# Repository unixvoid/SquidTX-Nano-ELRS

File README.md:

# SquidTX Nano

SquidTX Nano is a small 2.4Ghz ELRS TX board. It features an ESP32-WROOM-32E and an SX1280
and runs the stock ExpressLRS `DIY 2400 E28` target. An onboard TPS63802 buck-boost takes
1.3 V to 5.5 V and makes 3.3 V, so the board runs straight off a 1S battery. I designed
this to fit in a TBS Tango 2, but it'll work with anything.

The KiCad files, gerbers and photos are in this repo so you can build one.

<p align="center">
  
  <br>
  <em>Finished board, with the E28 module and its u.FL antenna</em>
  <br><br>

  <br>
  <em>Part-assembled front (E28-2G4M27S and u.FL antenna), part-assembled back (ESP32-WROOM-32E), bare PCB front, bare PCB back</em>
  <br><br>

  <br>
  <em>Copper and silkscreen: front (E28 side) and back (ESP32 side)</em>
  <br><br>
  
  <br>
  <em>Installed between the gimbals, with the three wires out to the module bay</em>
</p>

Full schematic: [docs/images/schematic.png](docs/images/schematic.png).

## Contents

- [Features](#features)
- [Specs](#specs)
- [Pin map](#pin-map)
- [Power](#power)
- [Connectors and wiring](#connectors-and-wiring)
- [Bill of materials](#bill-of-materials)
- [Firmware](#firmware)
- [Flashing](#flashing)
- [Manufacturing](#manufacturing)
- [Repo layout](#repo-layout)
- [License](#license)

## Features

- Runs the stock ExpressLRS `DIY 2400 E28` target.
- E28-2G4M27S does the RF: SX1280, PA and LNA, up to 27 dBm, with the PA and LNA enables driven by
  the firmware on IO26 and IO27.
- TPS63802 buck-boost, 1.3 V to 5.5 V in, 3.3 V out at up to 2 A, so no second regulator is needed.
- 20.0 x 35.5 mm, 2 layers, 1.6 mm FR-4, 0805 passives and a 1210 inductor.
- 6-pin SquidGrip pad array for the first flash and for recovery.
- Optional 2-pin fan header on IO17, which is the target's `misc_fan_en`.

## Specs

| Item | Value |
| --- | --- |
| Protocol | ExpressLRS 2.4 GHz, CRSF over a half-duplex UART |
| RF module | Ebyte E28-2G4M27S (SX1280 with PA and LNA), 2.4 to 2.5 GHz, 27 dBm |
| Antenna | u.FL/IPEX connector on the sx1280 module. I've used an external u.FL antenna in some of the photos |
| MCU | ESP32-WROOM-32E (ESP32-D0WD-V3, 4 MB flash) |
| Firmware target | `DIY 2400 E28`, legacy name `DIY_2400_TX_ESP32_SX1280_E28` |
| Minimum ExpressLRS version | 3.0.0 |
| Input voltage | 1.3 V to 5.5 V |
| Output | 3.3 V, up to 2 A (TPS63802DLAR buck-boost) |
| Power levels | 5, shown as 10 / 25 / 50 / 100 / 250 mW in the Lua script |
| Size | 20.0 x 35.5 mm, 0.5 mm corner radius |
| Connectors | J1 3-pin power and CRSF header, J2 2-pin fan header, SG1 6-pin SquidGrip port |
| LED, screen, button | none |

## Pin map

These are taken from the schematic, and they match the stock `DIY 2400 E28` target pin for pin,
which is why no firmware changes are needed.

### ESP32-WROOM-32E

| ESP32 pin | GPIO | Net name | Connects to | ELRS target key |
| --- | --- | --- | --- | --- |
| 29 | IO5 | `NSS_CTS/IO5` | E28 pin 6 (NSS_CTS) | `radio_nss: 5` |
| 30 | IO18 | `SCK/RTSN/IO18` | E28 pin 5 (SCK_RTSN) | `radio_sck: 18` |
| 31 | IO19 | `MISO_TX/IO19` | E28 pin 3 (MISO_TX) | `radio_miso: 19` |
| 37 | IO23 | `MOSI_RX/IO23` | E28 pin 4 (MOSI_RX) | `radio_mosi: 23` |
| 33 | IO21 | `BUSY/IO21` | E28 pin 12 (BUSY) | `radio_busy: 21` |
| 26 | IO4 | `DIO1/IO4` | E28 pin 13 (DIO1) | `radio_dio1: 4` |
| 13 | IO14 | `RESET/IO14` | E28 pin 11 (NRESET) | `radio_rst: 14` |
| 12 | IO27 | `RX_EN/IO27` | E28 pin 8 (RX_EN, LNA enable) | `power_rxen: 27` |
| 11 | IO26 | `TX_EN/IO26` | E28 pin 9 (TX_EN, PA enable) | `power_txen: 26` |
| 16 | IO13 | `ELRS_DUPLEX` | J1 pin 3 (CRSF) | `serial_rx: 13`, `serial_tx: 13` |
| 28 | IO17 | `FAN_CTRL/IO17` | J2 pin 2 (fan) | `misc_fan_en: 17` |
| 35 | TXD0/IO1 | `TX` | SG1 pin 5 (programmer RXD) | `debug_backpack_tx: 1` |
| 34 | RXD0/IO3 | `RX` | SG1 pin 6 (programmer TXD) | `debug_backpack_rx: 3` |
| 25 | IO0 | `IO0/FLASH` | SG1 pin 4 (programmer RTS) | boot strapping |
| 3 | EN | `EN` | R1 10 kΩ pull-up to 3V3, SG1 pin 2 (DTR) | - |
| 2 | VDD (3V3) | `+3.3V` | U2 VOUT, C1, C2, C4 | - |
| 1, 15, 38, 39 | GND | `GND` | ground plane | - |
| 24 | IO2 | `GND` | tied low (strapping pin) | (`screen_cs: 2`, unused) |

Not connected: `SENSOR_VP/VN`, IO34, IO35, IO32, IO33, IO25, IO12, IO15, IO16, IO22, the SDIO pins
(17 to 22) and NC (32).

### E28-2G4M27S (16 pins, 1.27 mm pitch)

| E28 pin | Name | Net | E28 pin | Name | Net |
| --- | --- | --- | --- | --- | --- |
| 1 | VCC | `+3.3V` | 9 | TX_EN | `TX_EN/IO26` |
| 2 | GND | `GND` | 10 | GND | `GND` |
| 3 | MISO_TX | `MISO_TX/IO19` | 11 | NRESET | `RESET/IO14` |
| 4 | MOSI_RX | `MOSI_RX/IO23` | 12 | BUSY | `BUSY/IO21` |
| 5 | SCK_RTSN | `SCK/RTSN/IO18` | 13 | DIO1 | `DIO1/IO4` |
| 6 | NSS_CTS | `NSS_CTS/IO5` | 14 | DIO2 | not connected |
| 7 | GND | `GND` | 15 | DIO3 | not connected |
| 8 | RX_EN | `RX_EN/IO27` | 16 | GND | `GND` |

## Power

U2 is a TPS63802 buck-boost. It takes the raw battery rail (1.3 V to 5.5 V) and makes the 3.3 V rail
for both modules, so there is no second regulator on the board.

| U2 pin | Name | Net | Notes |
| --- | --- | --- | --- |
| 1 | EN | `VIN/BATT` | tied to VIN, so the converter is always enabled |
| 2 | MODE | `GND` | mode pin tied low |
| 3 | AGND | `GND` | analog ground |
| 4 | FB | feedback divider | see below |
| 5 | PG | `Net-(U2-PG)` | 100 kΩ pull-up to VIN (R2), not routed to the MCU |
| 6 | VOUT | `+3.3V` | output, C4 is 22 µF |
| 7 | L2 | `Net-(U2-L2)` | to L1 |
| 8 | GND | `GND` | power ground |
| 9 | L1 | `Net-(U2-L1)` | to L1 |
| 10 | VIN | `VIN/BATT` | input, C3 is 10 µF |

Output voltage comes from the feedback divider, VOUT = VFB x (1 + R3/R4), and the TPS63802 reference
is 0.5 V:

```
0.5 V x (1 + 56k / 10k) = 3.3 V
```

L1 is 0.47 µH in a 1210 package. Pick one with a saturation current above the TPS63802's switch
current limit, so 2 A or more. The E28 module pulls around 0.6 A at 3.3 V when it is at full power.

C1 (4.7 µF) and C2 (0.1 µF) decouple the 3.3 V rail at the modules. C3 (10 µF) is the converter input
cap and C4 (22 µF) is the output cap.

## Connectors and wiring

| Ref | Type | Pin | Net | Notes |
| --- | --- | --- | --- | --- |
| J1 "INPUTS" | 1x3, 2.54 mm | 1 | `VIN/BATT` | 1.3 V to 5.5 V |
| | | 2 | `GND` | ground |
| | | 3 | `ELRS_DUPLEX` | CRSF to the radio (IO13) |
| J2 "Fan" | 1x2, 2.54 mm | 1 | `GND` | fan negative |
| | | 2 | `FAN_CTRL/IO17` | fan positive, switched by `misc_fan_en` |
| SG1 "SquidGrip" | 2x3, 1.27 mm | 1 | `GND` | programmer ground |
| | | 2 | `EN` | ESP32 reset (programmer DTR) |
| | | 3 | `+3.3V` | 3.3 V out to the programmer |
| | | 4 | `IO0/FLASH` | boot select (programmer RTS) |
| | | 5 | `TX` (IO1) | ESP32 TXD0 to programmer RXD |
| | | 6 | `RX` (IO3) | ESP32 RXD0 to programmer TXD |

J1 is the only connection the module needs: power, ground and the CRSF signal. Wire those three to
whatever radio you are using. J2 is optional, and SG1 is only for flashing.

J1 and J2 are 2.54 mm through-hole headers on the front. SG1 is a 1.27 mm 2x3 pad array that mates
with a SquidGrip probe. The SquidGrip is a USB-UART probe I designed around a CP2102N, with the ESP32
auto-reset circuit on it (DTR to EN, RTS to IO0). It is a thin PCB tongue that clamps onto a bare
board with an alligator clip style grip, and it is a cheap alternative to Tag-Connect. Its design
files are in the [SquidGrip repo](https://github.com/unixvoid/squidgrip), and the pad array on its own
is here as `hardware/squidgrip_pogo_2x03_P1.27mm.kicad_mod`.

## Bill of materials

| Ref | Value / Part | Package | Notes |
| --- | --- | --- | --- |
| U1 | Espressif ESP32-WROOM-32E (4 MB) | module, 18 x 25.5 mm | MCU, WiFi and BT (used for WiFi updates) |
| U2 | TI TPS63802DLAR | 10-pin DLA (VQFN-HR) | buck-boost, 1.3 to 5.5 V in, 3.3 V out, 2 A |
| E28-2G4M27S1 | Ebyte E28-2G4M27S | 16-pin SMD, 1.27 mm pitch, about 15 x 26.5 mm | SX1280 with PA and LNA, 27 dBm. PCB antenna or u.FL, selected by a resistor on the module (this build uses u.FL) |
| L1 | 0.47 µH | 1210 (3225 metric) | 2 A saturation or better |
| C1 | 4.7 µF | 0805 | 3V3 decoupling |
| C2 | 0.1 µF | 0805 | 3V3 decoupling |
| C3 | 10 µF | 0805 | VIN input cap |
| C4 | 22 µF | 0805 | VOUT output cap |
| R1 | 10 kΩ | 0805 | ESP32 EN pull-up to 3V3 |
| R2 | 100 kΩ | 0805 | PG pull-up to VIN |
| R3 | 56 kΩ | 0805 | feedback divider, top |
| R4 | 10 kΩ | 0805 | feedback divider, bottom |
| - | 2.4 GHz antenna and u.FL pigtail | external | not on the PCB. The E28 needs an antenna on its u.FL (this build uses a Seeed Studio XIAO FPC Antenna A-01) |

## Firmware

This board runs a stock ExpressLRS target. There is no custom target and no `user_defines` to set.

| | |
| --- | --- |
| Target in the Configurator | DIY ESP32 E28 2.4GHz TX (vendor: DIY) |
| Unified target name | `DIY 2400 E28` |
| Legacy target name | `DIY_2400_TX_ESP32_SX1280_E28` |
| Firmware binary | `Unified_ESP32_2400_TX` |
| Minimum ELRS version | 3.0.0 |
| Upload methods | UART, WiFi |
| Target features | fan |

The target's pins match this board, including the half-duplex CRSF line on IO13, the PA and LNA
enables on IO26 and IO27, and the fan output on IO17.

A few target settings go unused here: `led_rgb` (IO15), the screen pins (2, 22, 32, 33, 16),
`power_lna_gain` (IO12) and the ESP backpack.

## Flashing

### First flash over UART

Use a SquidGrip if you have one, otherwise any 3.3 V USB-UART adapter (CP2102, FT232, CH340 and so
on) wired to SG1:

| USB-UART adapter | SG1 pin | Notes |
| --- | --- | --- |
| GND | 1 | required |
| DTR | 2 | ESP32 EN (reset) |
| 3V3 | 3 | optional, the board can also be powered from J1 |
| RTS | 4 | ESP32 IO0 (boot select) |
| RXD | 5 | to the ESP32's TX (IO1) |
| TXD | 6 | to the ESP32's RX (IO3) |

Then pick the target above in the Configurator, set the upload method to UART, choose the COM port
and press Build & Flash.

The board wires DTR straight to EN and RTS straight to IO0. The auto-reset logic lives in the
SquidGrip (or in whatever programmer you use), not on the board, so a plain adapter without that
circuit may not reset the ESP32 on its own. If that happens, put it into boot mode by hand: hold
IO0 (SG1 pin 4) to GND, pulse EN (SG1 pin 2) to GND, release IO0, then start the flash.

### Updates over WiFi

ESP32 targets can be flashed over WiFi, so after the first UART flash you do not have to take
anything apart:

1. In the radio's ELRS Lua script, start the WiFi update. The module reboots into access point mode.
2. Join its network (the ELRS defaults are SSID `ExpressLRS TX` and password `expresslrs`).
3. Use the Configurator's WiFi method, or open `http://10.0.0.1` and use the web UI.

### Binding

There is no bind button on the board, so bind from the ELRS Lua script. The Lua script is also where
you read link status, since there is no status LED either.

## Manufacturing

Everything you need to order the board is in `hardware/`:

| File | Description |
| --- | --- |
| `hardware/squidtx_nano.kicad_pro` | KiCad project (design rules and netclass) |
| `hardware/squidtx_nano.kicad_sch` | schematic (title block: SquidTX Nano, rev v1, Midnight CAD) |
| `hardware/squidtx_nano.kicad_pcb` | PCB layout |
| `hardware/manufacturing/squidtx_nano-v1-gerbers.zip` | gerber and drill package, ready to upload |
| `hardware/manufacturing/gerbers/` | the same files unpacked (F and B Cu, mask, paste, silk, Edge_Cuts, drill, job) |
| `hardware/squidgrip_pogo_2x03_P1.27mm.kicad_mod` | the 6-pin SquidGrip pad array on its own, for your own boards |
| `docs/images/` | photos, renders and the schematic image used here |

## Repo layout

```
.
├── README.md
├── LICENSE                      # CERN-OHL-S-2.0
├── docs/
│   └── images/
│       ├── squidtx_nano.gif            # gif, finished board in hand
│       ├── squidtx_nano_front.jpg      # photo, board front (E28 side)
│       ├── squidtx_nano_back.jpg       # photo, board back (ESP32 side)
│       ├── squidtx_nano_pcb_front.jpg  # photo, bare PCB front
│       ├── squidtx_nano_pcb_back.jpg   # photo, bare PCB back
│       ├── squidtx_nano_installed.jpg  # photo, board installed in the radio
│       ├── board-front.png             # KiCad render, front copper and silk
│       ├── board-back.png              # KiCad render, back copper and silk
│       └── schematic.png               # schematic image
└── hardware/
    ├── squidtx_nano.kicad_pro   # KiCad project
    ├── squidtx_nano.kicad_sch   # schematic
    ├── squidtx_nano.kicad_pcb   # PCB layout
    ├── squidgrip_pogo_2x03_P1.27mm.kicad_mod   # the 6-pin SquidGrip pad array
    └── manufacturing/
        ├── squidtx_nano-v1-gerbers.zip
        └── gerbers/             # unpacked gerbers and drill files
```

## License

SquidTX Nano is licensed under the CERN Open Hardware Licence Version 2 - Strongly Reciprocal
(CERN-OHL-S-2.0). The full licence text is in [`LICENSE`](LICENSE).

```
Copyright (C) 2026 Midnight CAD / SquidTX

This source describes Open Hardware and is licensed under the CERN-OHL-S v2.

You may redistribute and modify this source and make products using it under
the terms of the CERN-OHL-S v2 (https://ohwr.org/cern_ohl_s_v2.txt).

This source is distributed WITHOUT ANY EXPRESS OR IMPLIED WARRANTY, INCLUDING
OF MERCHANTABILITY, SATISFACTORY QUALITY AND FITNESS FOR A PARTICULAR PURPOSE.
Please see the CERN-OHL-S v2 for applicable conditions.

Source location: https://github.com/unixvoid/SquidTX-Nano-ELRS
```

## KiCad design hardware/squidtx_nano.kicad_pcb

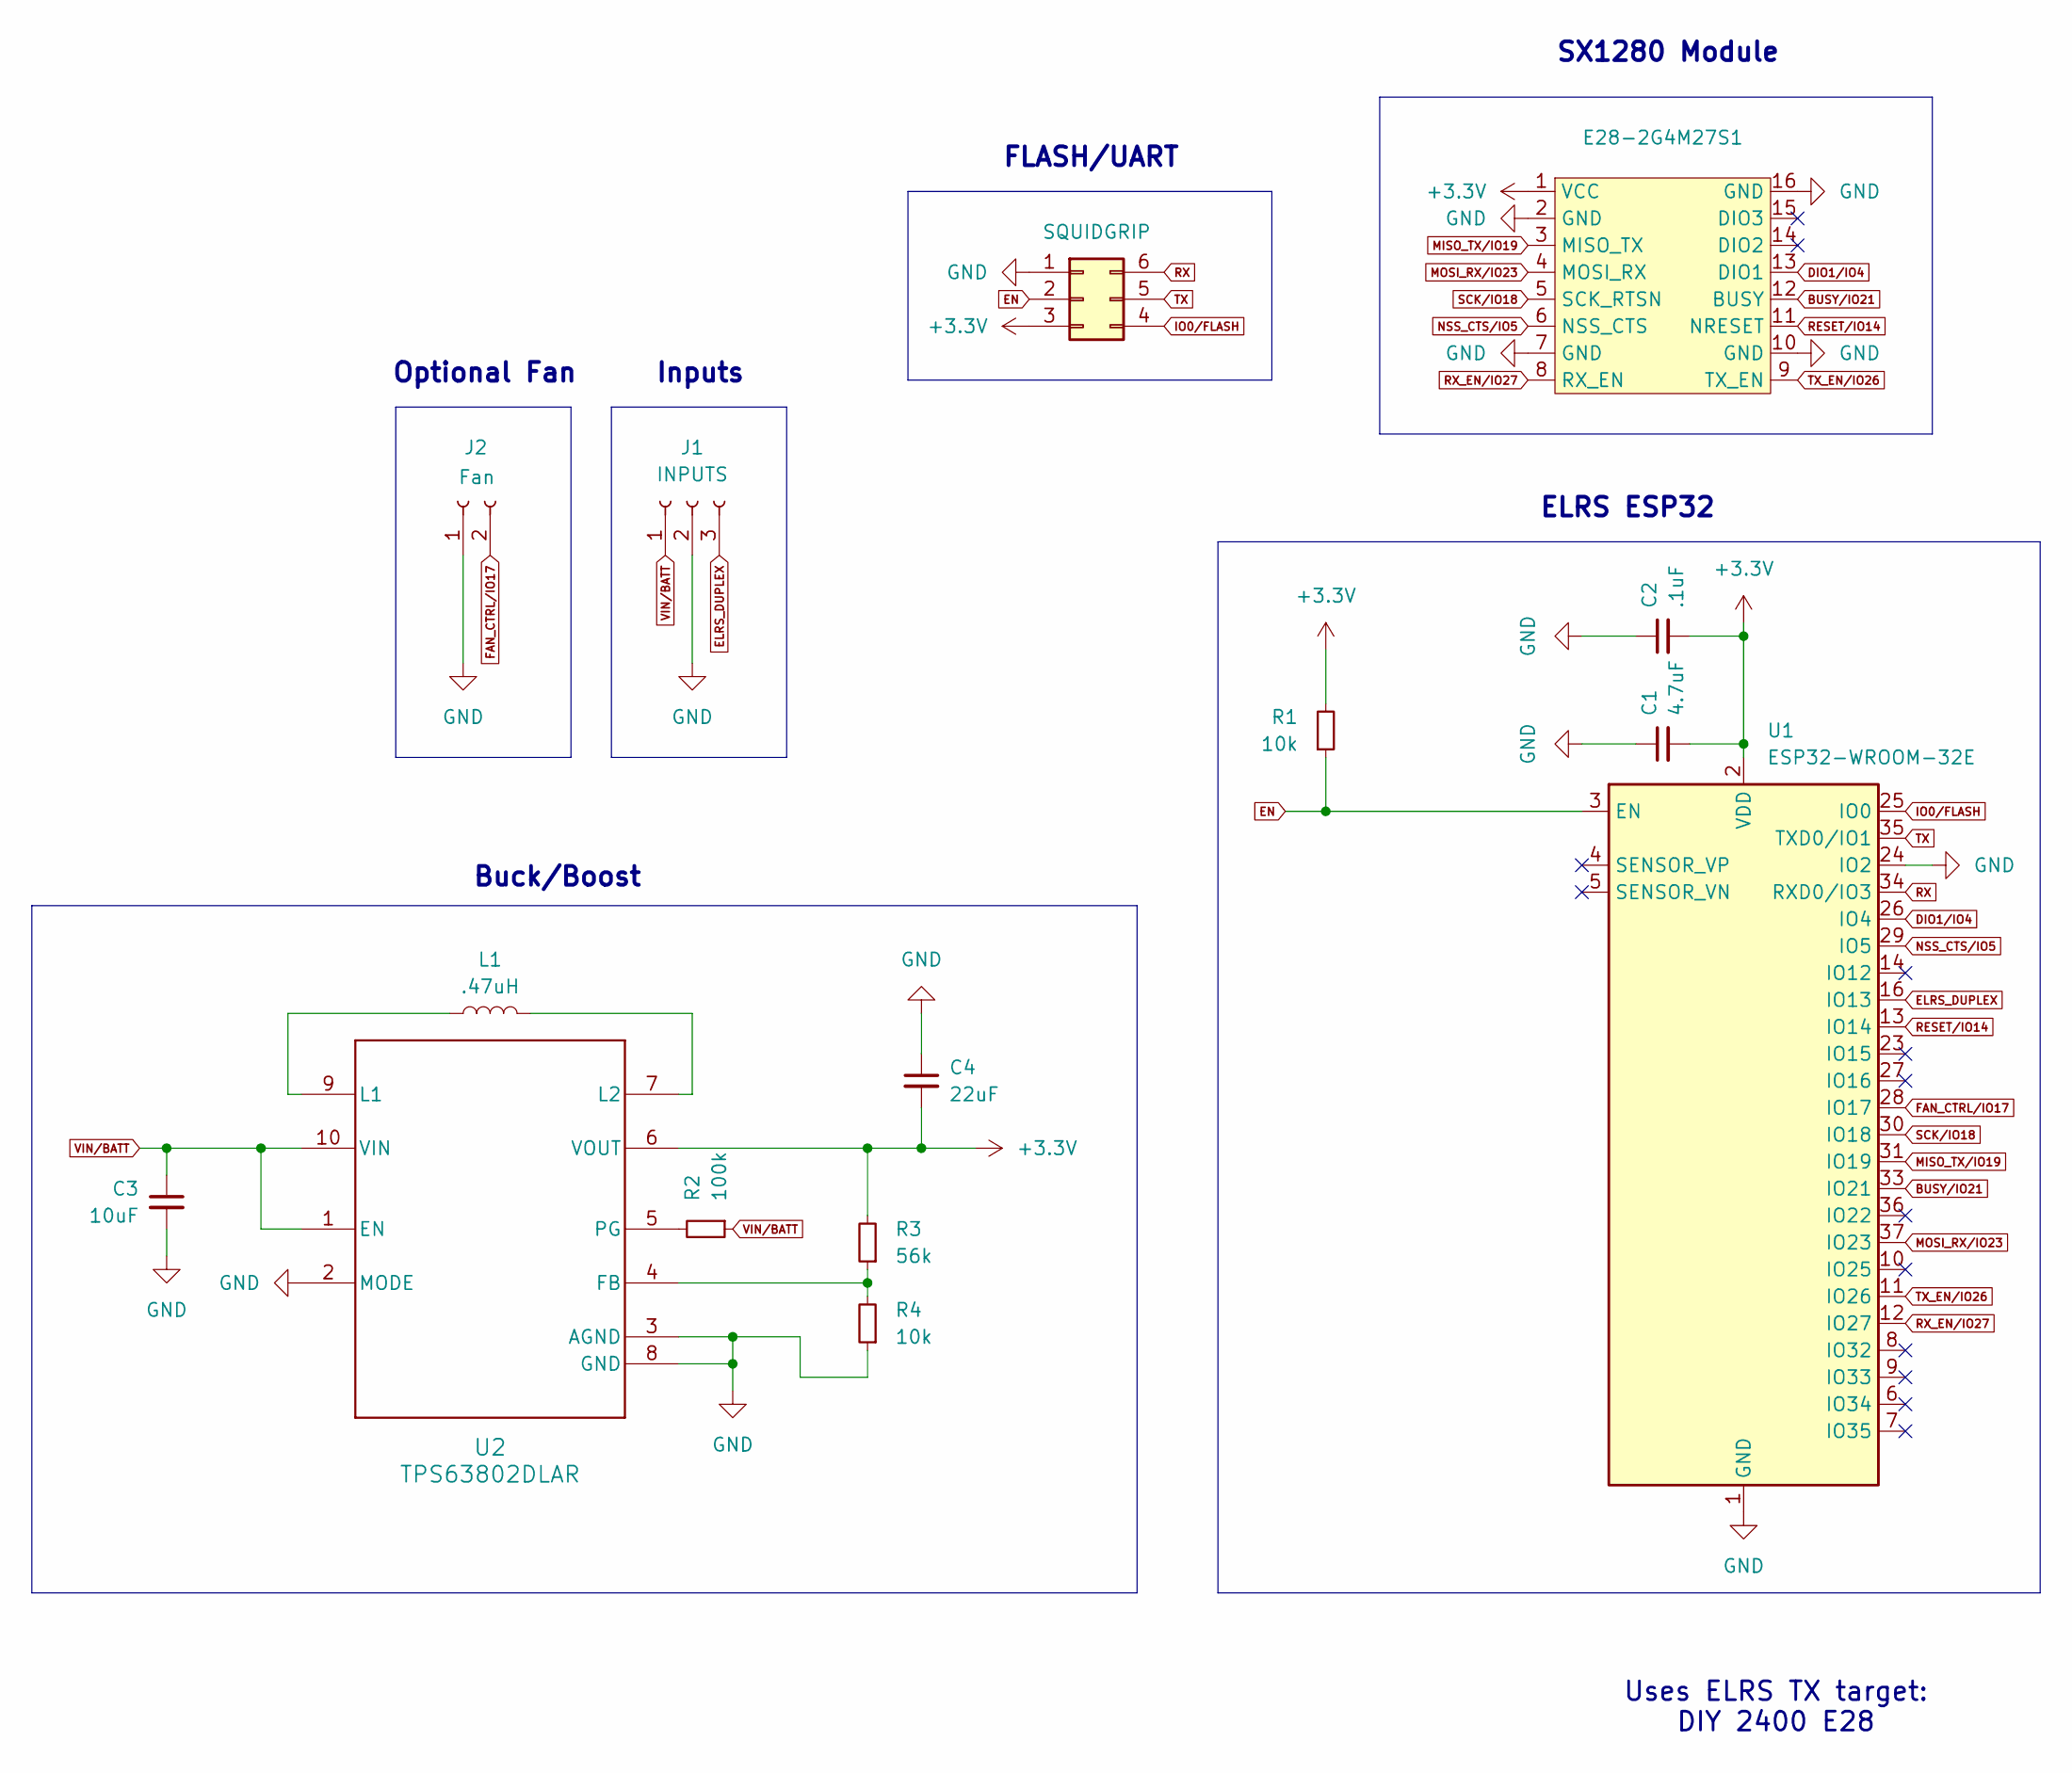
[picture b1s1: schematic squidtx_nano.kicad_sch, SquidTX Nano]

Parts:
C1: 4.7uF; C_0805_2012Metric
C2: .1uF; C_0805_2012Metric
C3: 10uF; C_0805_2012Metric
C4: 22uF; C_0805_2012Metric
E28-2G4M27S1: E28-2G4M27S
J1: INPUTS; PinHeader_1x03_P2.54mm_Vertical
J2: Fan; PinHeader_1x02_P2.54mm_Vertical
L1: .47uH; L_1210_3225Metric
R1, R4: 10k; R_0805_2012Metric
R2: 100k; R_0805_2012Metric
R3: 56k; R_0805_2012Metric
SG1: SQUIDGRIP; squidgrip
U1: ESP32-WROOM-32E; ESP32-WROOM-32D
U2: TPS63802DLAR

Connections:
+3.3V: C1.2, C2.2, C4.2, E28-2G4M27S1.1 (VCC), R1.2, R3.2, SG1.3 (3.3v), U1.2 (VDD), U2.6 (VOUT)
BUSY/IO21: E28-2G4M27S1.12 (BUSY), U1.33 (IO21)
DIO1/IO4: E28-2G4M27S1.13 (DIO1), U1.26 (IO4)
ELRS_DUPLEX: J1.3, U1.16 (IO13)
EN: R1.1, SG1.2 (DTR), U1.3 (EN)
FAN_CTRL/IO17: J2.2, U1.28 (IO17)
GND: C1.1, C2.1, C3.2, C4.1, E28-2G4M27S1.2 (GND), E28-2G4M27S1.7 (GND), E28-2G4M27S1.10 (GND), E28-2G4M27S1.16 (GND), J1.2, J2.1, R4.1, SG1.1 (GND), U1.1 (GND), U1.15 (GND), U1.24 (IO2), U1.38 (GND), U1.39 (GND), U2.2 (MODE), U2.3 (AGND), U2.8 (GND)
IO0/FLASH: SG1.4 (RTS), U1.25 (IO0)
MISO_TX/IO19: E28-2G4M27S1.3 (MISO_TX), U1.31 (IO19)
MOSI_RX/IO23: E28-2G4M27S1.4 (MOSI_RX), U1.37 (IO23)
NSS_CTS/IO5: E28-2G4M27S1.6 (NSS_CTS), U1.29 (IO5)
unnamed: R3.1, R4.2, U2.4 (FB)
unnamed: L1.1, U2.9 (L1)
unnamed: L1.2, U2.7 (L2)
unnamed: R2.2, U2.5 (PG)
RESET/IO14: E28-2G4M27S1.11 (NRESET), U1.13 (IO14)
RX: SG1.6 (TXD), U1.34 (RXD0/IO3)
RX_EN/IO27: E28-2G4M27S1.8 (RX_EN), U1.12 (IO27)
SCK/IO18: E28-2G4M27S1.5 (SCK_RTSN), U1.30 (IO18)
TX: SG1.5 (RXD), U1.35 (TXD0/IO1)
TX_EN/IO26: E28-2G4M27S1.9 (TX_EN), U1.11 (IO26)
VIN/BATT: C3.1, J1.1, R2.1, U2.1 (EN), U2.10 (VIN)

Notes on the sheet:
Inputs
Optional Fan
FLASH/UART
SX1280 Module
Buck/Boost
ELRS ESP32
Uses ELRS TX target: DIY 2400 E28

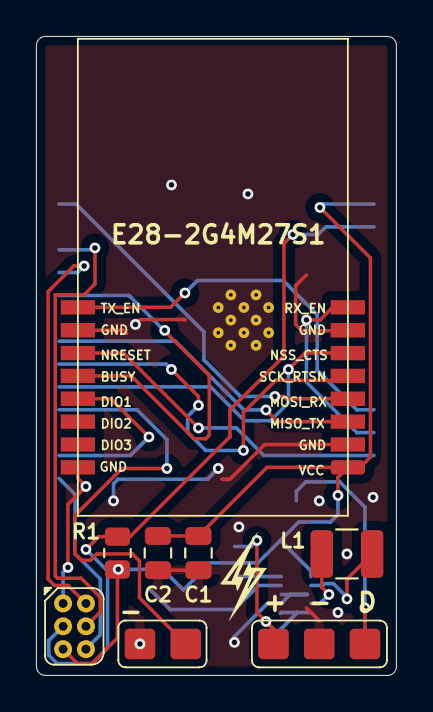
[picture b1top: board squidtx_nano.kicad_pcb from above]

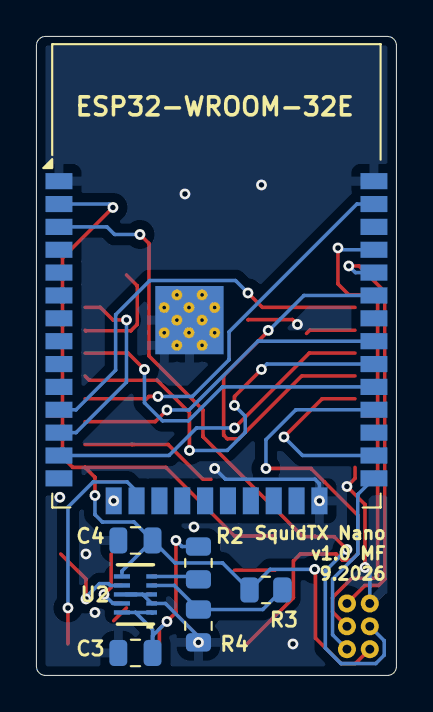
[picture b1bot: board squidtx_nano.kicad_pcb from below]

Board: 2 copper layers, 20.0 x 35.5 mm, 15 parts (7 on the bottom side), 22 nets.
